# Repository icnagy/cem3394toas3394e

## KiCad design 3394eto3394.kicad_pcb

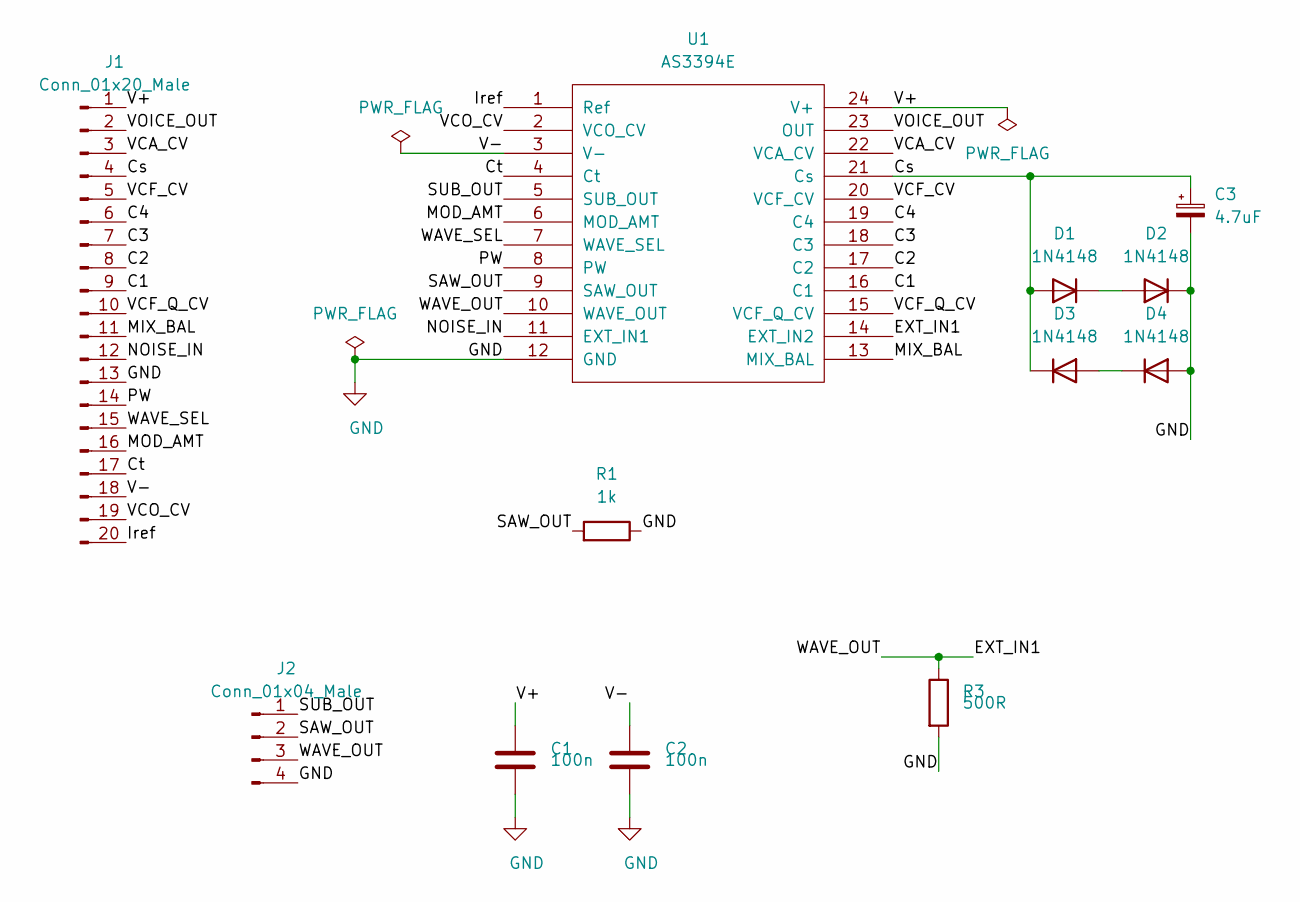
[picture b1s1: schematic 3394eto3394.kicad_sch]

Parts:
C1, C2: 100n; C_Rect_L7.0mm_W3.5mm_P2.50mm_P5.00mm
C3: 4.7uF; CP_Radial_D5.0mm_P2.50mm
D1, D2, D3, D4: 1N4148; D_DO-35_SOD27_P2.54mm_Vertical_AnodeUp
J1: Conn_01x20_Male; DIP-20_W7.62mm_LongPads
J2: Conn_01x04_Male; PinHeader_1x04_P2.54mm_Vertical
R1: 1k; R_Axial_DIN0207_L6.3mm_D2.5mm_P2.54mm_Vertical
R3: 500R; R_Axial_DIN0207_L6.3mm_D2.5mm_P2.54mm_Vertical
U1: AS3394E; DIP-24_W7.62mm_LongPads

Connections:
/C1: J1.9, U1.16 (C1)
/C2: J1.8, U1.17 (C2)
/C3: J1.7, U1.18 (C3)
/C4: J1.6, U1.19 (C4)
/Cs: C3.1, D1.2 (A), D3.1 (K), J1.4, U1.21 (Cs)
/Ct: J1.17, U1.4 (Ct)
/EXT_IN1: J2.3, R3.1, U1.10 (WAVE_OUT), U1.14 (EXT_IN2)
/Iref: J1.20, U1.1 (Ref)
/MIX_BAL: J1.11, U1.13 (MIX_BAL)
/MOD_AMT: J1.16, U1.6 (MOD_AMT)
/NOISE_IN: J1.12, U1.11 (EXT_IN1)
/PW: J1.14, U1.8 (PW)
/SAW_OUT: J2.2, R1.2, U1.9 (SAW_OUT)
/SUB_OUT: J2.1, U1.5 (SUB_OUT)
/V+: C1.1, J1.1, U1.24 (V+)
/V-: C2.1, J1.18, U1.3 (V-)
/VCA_CV: J1.3, U1.22 (VCA_CV)
/VCF_CV: J1.5, U1.20 (VCF_CV)
/VCF_Q_CV: J1.10, U1.15 (VCF_Q_CV)
/VCO_CV: J1.19, U1.2 (VCO_CV)
/VOICE_OUT: J1.2, U1.23 (OUT)
/WAVE_SEL: J1.15, U1.7 (WAVE_SEL)
GND: C1.2, C2.2, C3.2, D2.1 (K), D4.2 (A), J1.13, J2.4, R1.1, R3.2, U1.12 (GND)
unnamed: D1.1 (K), D2.2 (A)
unnamed: D3.2 (A), D4.1 (K)

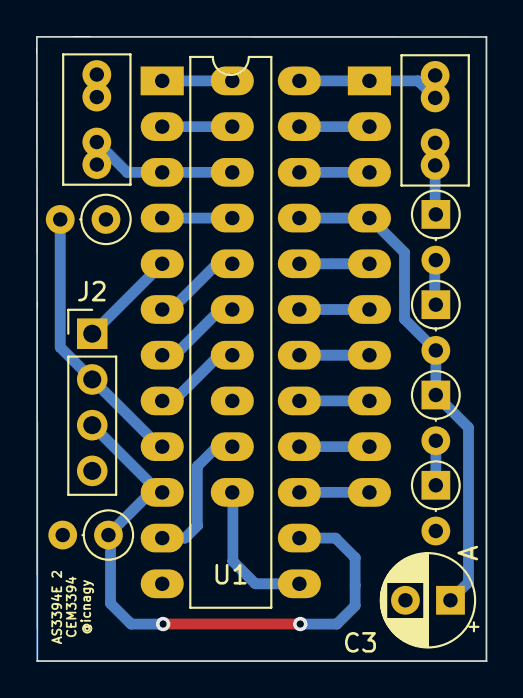
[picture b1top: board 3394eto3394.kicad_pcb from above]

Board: 2 copper layers, 25.0 x 34.7 mm, 12 parts (1 on the bottom side), 25 nets.

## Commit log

2020-11-13 Version 2
2022-02-24 Upgrade to kicad 6, add missing capacitor
